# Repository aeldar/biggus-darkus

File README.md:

# Biggus Darkus

An Elite Dangerous companion tool: a custom hardware device that shows live game information, driven by a desktop app that reads the game's journal and state files.

## Parts

| Folder | What it is | Status |
|---|---|---|
| [`firmware`](firmware/) | Firmware for the custom device (Arduino Nano, LED strip, TM1637 digit displays, 16×2 LCD, mode button) | Working |
| [`app`](app/) | Desktop app (Rust, Tauri, React) that reads Elite Dangerous journals and state, and sends them to the device over serial. Its GUI sets the serial port, the journal location and the rules for how the device reacts to game events and state. Also has a headless CLI. | Working; tested with the real device and game, bugs still being collected |
| [`pcb`](pcb/) | KiCad design for the device board, built on a perfboard. Build and wiring guide: [`pcb/wiring.md`](pcb/wiring.md) | In progress |

## How it fits together

```
Elite Dangerous  ->  journal + state files  ->  desktop app  ->  serial commands  ->  device
```

The app turns game events into serial commands using editable rules. The firmware's command protocol is in [`firmware/docs/commands.md`](firmware/docs/commands.md); the app has a typed copy of it, with generated docs, in [`app/docs/protocol.md`](app/docs/protocol.md).

## For developers and AI sessions

- App design, decisions and known gaps: [`app/docs/architecture.md`](app/docs/architecture.md)
- App build, run and packaging: [`app/README.md`](app/README.md)
- Firmware docs: [`firmware/docs/`](firmware/docs/)
- Elite Dangerous journal format (official): <https://elite-journal.readthedocs.io/en/latest/>

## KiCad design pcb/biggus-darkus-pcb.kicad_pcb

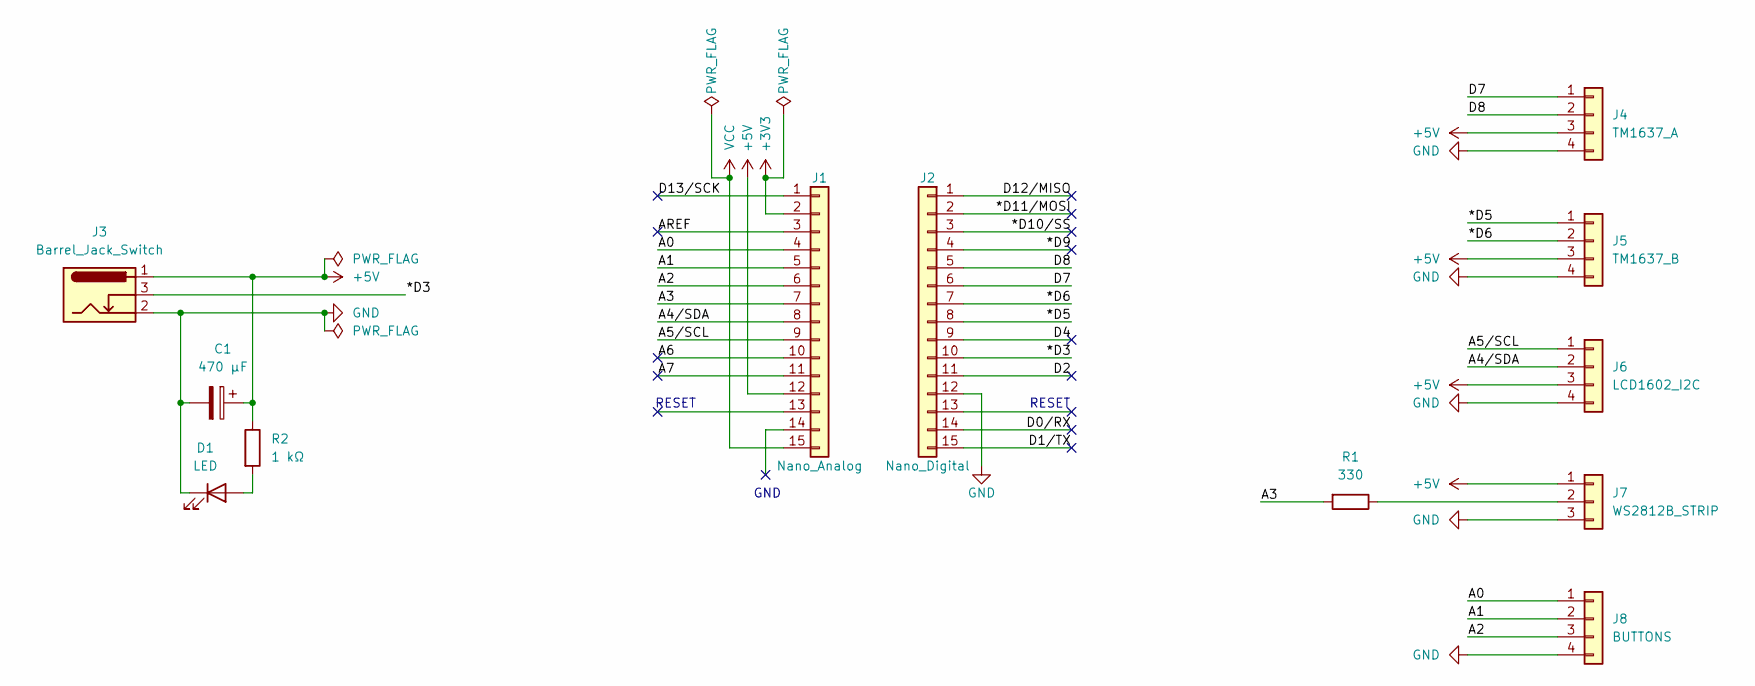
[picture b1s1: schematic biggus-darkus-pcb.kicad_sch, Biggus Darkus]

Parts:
C1: 470 µF; CP_Radial_D6.3mm_P2.50mm
D1: LED; LED_D5.0mm
J1: Nano_Analog; PinSocket_1x15_P2.54mm_Vertical
J2: Nano_Digital; PinSocket_1x15_P2.54mm_Vertical
J3: Barrel_Jack_Switch; BarrelJack_Horizontal
J4: TM1637_A; JST_XH_S4B-XH-A_1x04_P2.50mm_Horizontal
J5: TM1637_B; JST_XH_S4B-XH-A_1x04_P2.50mm_Horizontal
J6: LCD1602_I2C; JST_XH_S4B-XH-A_1x04_P2.50mm_Horizontal
J7: WS2812B_STRIP; JST_XH_S3B-XH-A_1x03_P2.50mm_Horizontal
J8: BUTTONS; JST_XH_S4B-XH-A_1x04_P2.50mm_Horizontal
R1: 330; R_Axial_DIN0207_L6.3mm_D2.5mm_P10.16mm_Horizontal
R2: 1 kΩ; R_Axial_DIN0207_L6.3mm_D2.5mm_P10.16mm_Horizontal

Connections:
+3V3: J1.2
+5V: C1.1, J1.12, J3.1, J4.3, J5.3, J6.3, J7.1, R2.1
/*D3: J2.10, J3.3
/*D5: J2.8, J5.1
/*D6: J2.7, J5.2
/*D9: J2.4
/*D10/SS: J2.3
/*D11/MOSI: J2.2
/A0: J1.4, J8.1
/A1: J1.5, J8.2
/A2: J1.6, J8.3
/A3: J1.7, R1.2
/A4/SDA: J1.8, J6.2
/A5/SCL: J1.9, J6.1
/A6: J1.10
/A7: J1.11
/AREF: J1.3
/D0/RX: J2.14
/D1/TX: J2.15
/D2: J2.11
/D4: J2.9
/D7: J2.6, J4.1
/D8: J2.5, J4.2
/D12/MISO: J2.1
/D13/SCK: J1.1
GND: C1.2, D1.1 (K), J2.12, J3.2, J4.4, J5.4, J6.4, J7.3, J8.4
unnamed: D1.2 (A), R2.2
unnamed: J7.2, R1.1
VCC: J1.15

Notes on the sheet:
GND
RESET

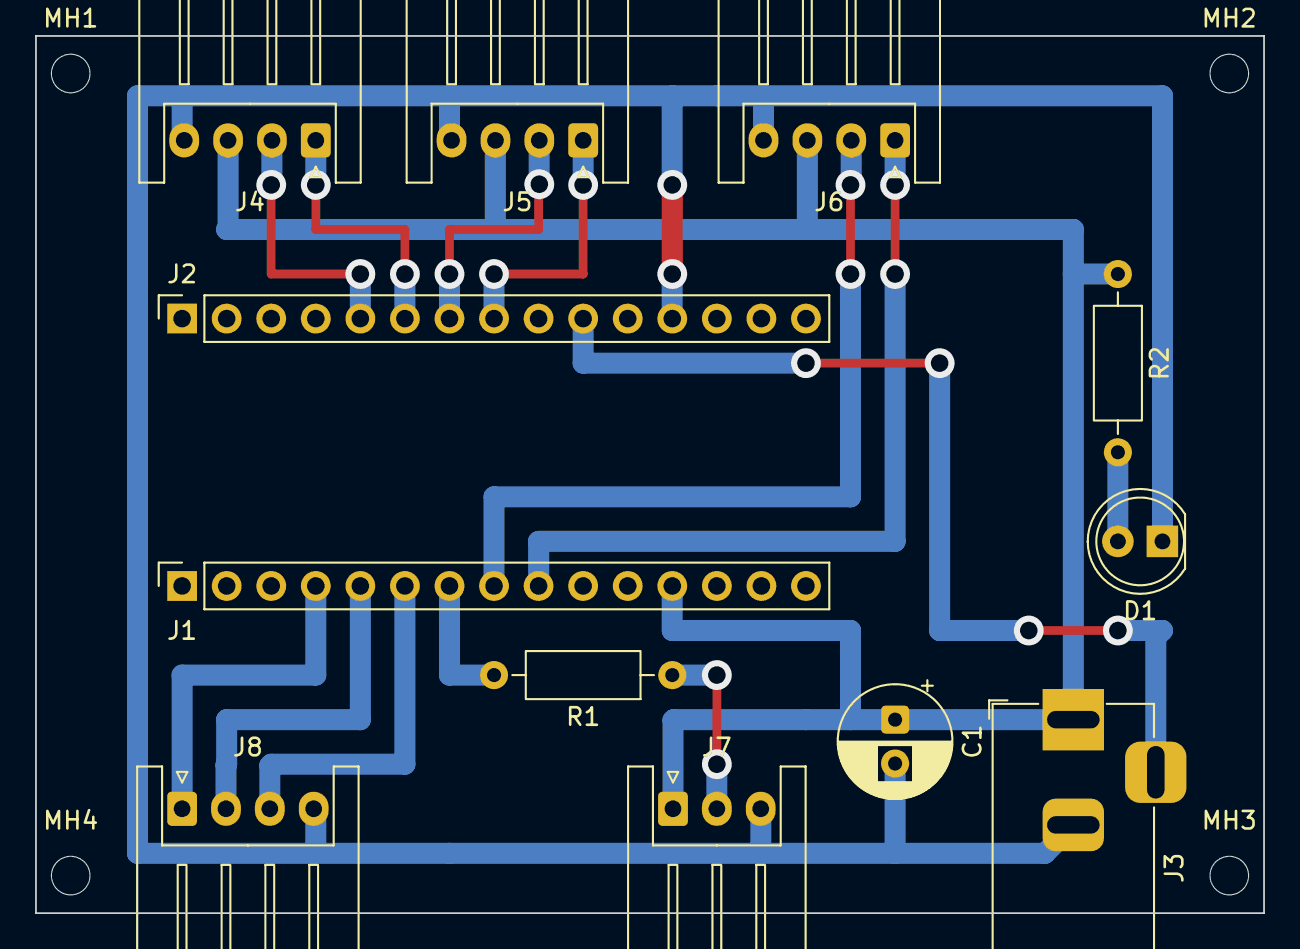
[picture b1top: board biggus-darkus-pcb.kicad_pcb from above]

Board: 2 copper layers, 70.0 x 50.0 mm, 16 parts (0 on the bottom side), 15 nets.

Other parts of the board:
MH1, MH2, MH3, MH4: MountingHole_2.2mm_M2
